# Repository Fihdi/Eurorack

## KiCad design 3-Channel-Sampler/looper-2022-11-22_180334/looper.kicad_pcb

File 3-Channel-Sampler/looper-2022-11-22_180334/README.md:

3 Channel Sampler that pairs well with the A, B and C outputs of my sequencer

This module sounds really bad because I used ISD1820 ICs for the sampling, which are low quality. I made a new Project "SimpleSampler" that uses a Daisy Seed to store and play Samples.

Known Issue: The solder points for the buttons are too close to the hole.
When the push button is stuck through the PCB and tightend with a washer, the washer will make contact with both solder points and the button is effectively always pressed.
I have put some small sheets of isolating rubber underneath the buttons to prevent this issue.

The summing amplifier should have a gain of two since the ISD1820 are running on 5V and are rather quiet compared to normal eurorack levels.

Sources and Inspiration:

https://bastl-instruments.com/support/tutorials/omsynth-project-3
https://www.youtube.com/watch?v=epjCe3o5BPA

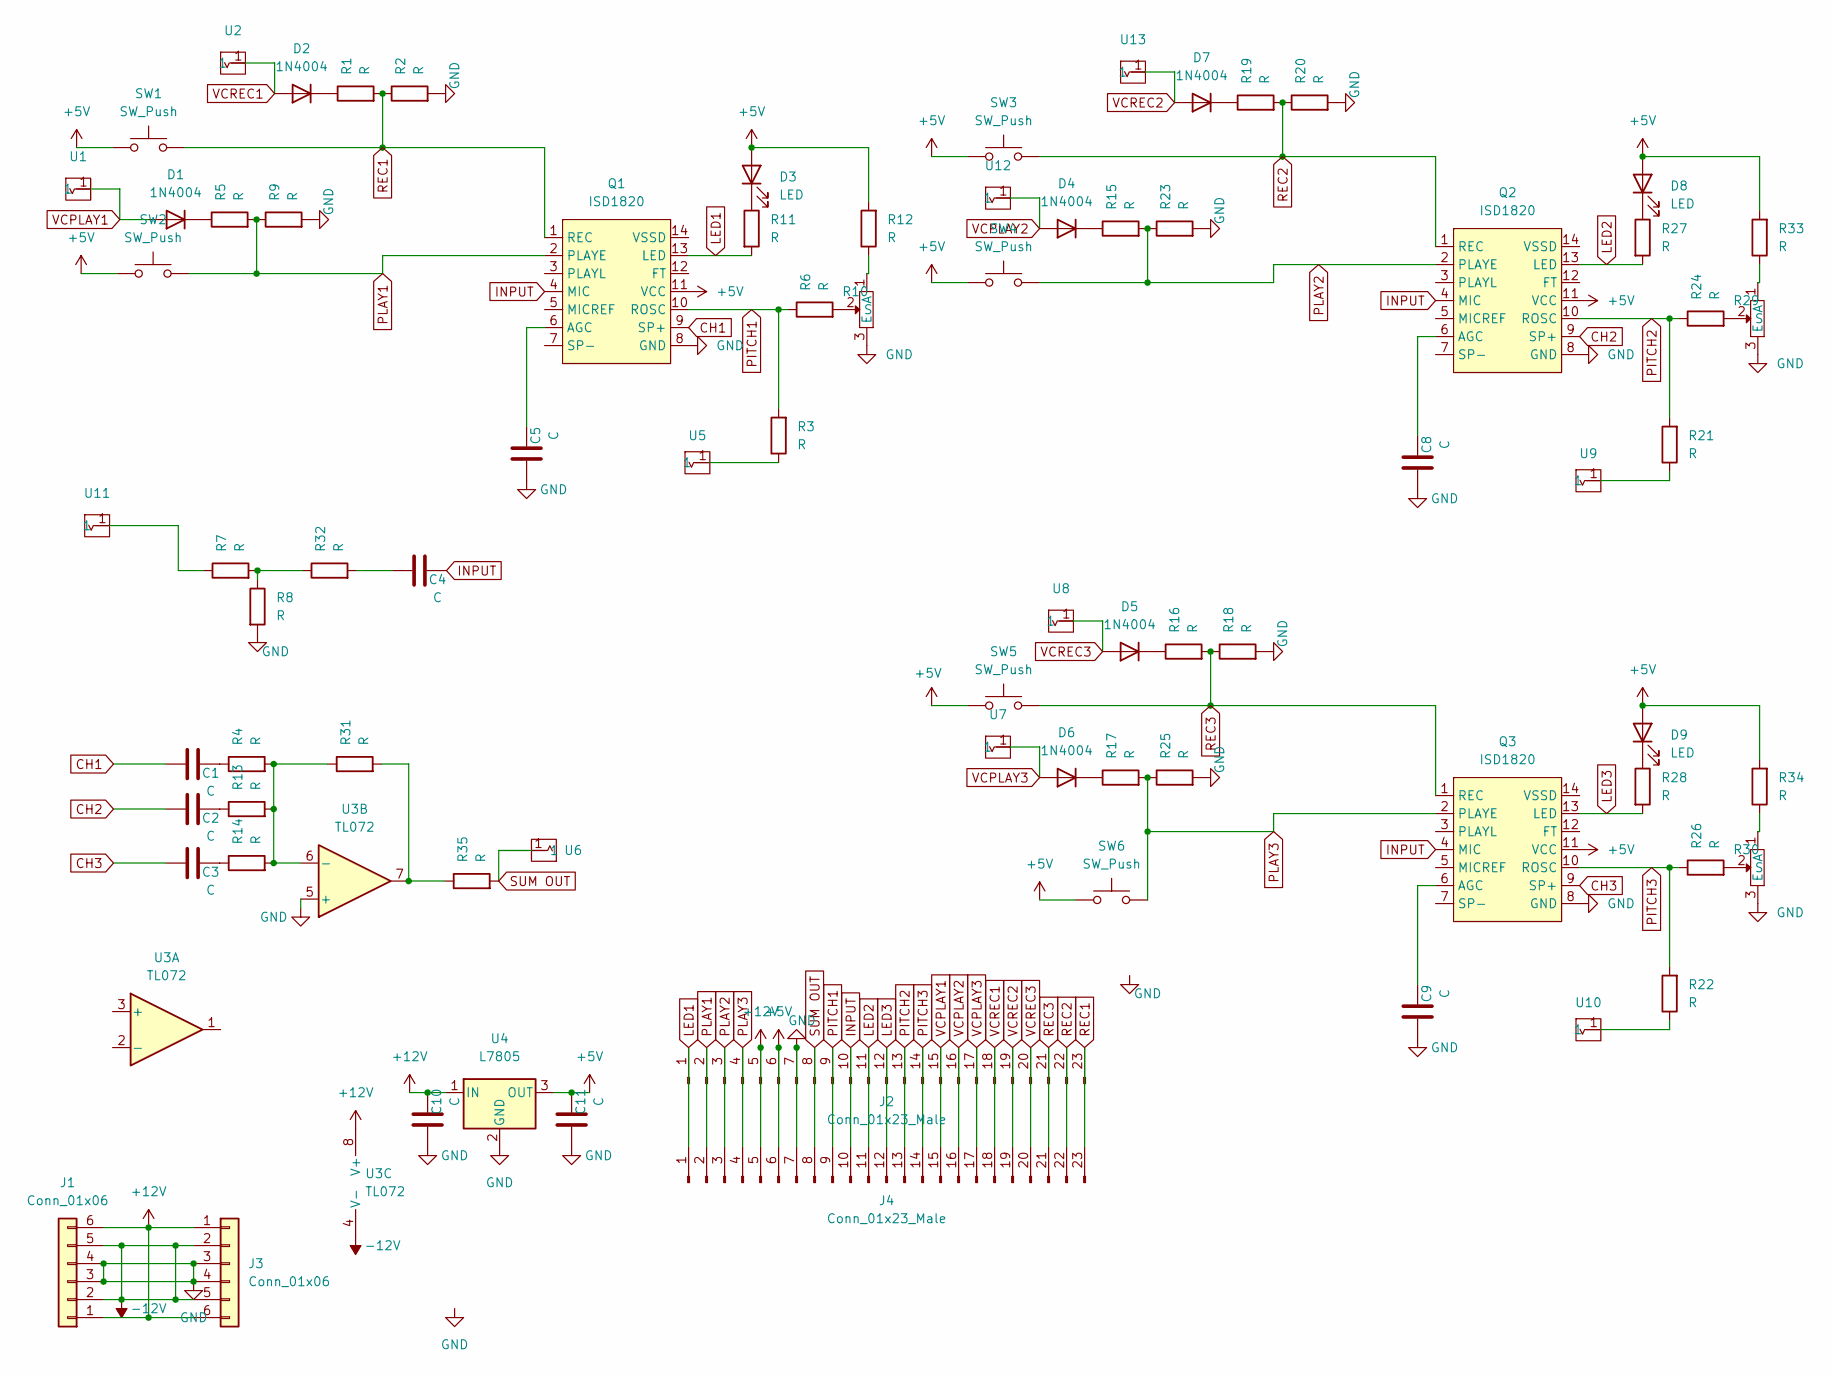
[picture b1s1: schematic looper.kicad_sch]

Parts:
C1, C2, C3: C; C_Axial_L3.8mm_D2.6mm_P7.50mm_Horizontal
C4, C5, C8, C9, C10, C11: C; C_Axial_L3.8mm_D2.6mm_P10.00mm_Horizontal
D1, D2, D4, D5, D6, D7: 1N4004; D_DO-41_SOD81_P7.62mm_Horizontal
D3, D8, D9: LED; LED_D5.0mm
J1, J3: Conn_01x06; PinHeader_1x06_P2.54mm_Vertical
J2, J4: Conn_01x23_Male; PinHeader_1x23_P2.54mm_Vertical
Q1, Q2, Q3: ISD1820; DIP-14_W7.62mm
R1, R2, R3, R4, R5, R6, R7, R8, R9, R11, R12, R13, R14, R15, R16, R17, R18, R19, R20, R21, R22, R23, R24, R25, R26, R27, R28, R31, R32, R33, R34, R35: R; R_Axial_DIN0207_L6.3mm_D2.5mm_P10.16mm_Horizontal
R10, R29, R30: AlpsPot
SW1, SW2, SW3, SW4, SW5, SW6: SW_Push; PushButton
U1, U2, U5, U6, U7, U8, U9, U10, U11, U12, U13: Aux_flush; aux_flush
U3: TL072; DIP-8_W7.62mm_Socket
U4: L7805; TO-220-3_Vertical

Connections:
+5V: C11.2, D3.2 (A), D8.2 (A), D9.2 (A), J2.6, J4.6, Q1.11 (VCC), Q2.11 (VCC), Q3.11 (VCC), R12.2, R33.2, R34.2, SW1.1, SW2.1, SW3.1, SW4.1, SW5.1, SW6.1, U4.3 (OUT)
+12V: C10.2, J1.1, J1.6, J2.5, J3.1, J3.6, J4.5, U3.8 (V+), U4.1 (IN)
-12V: J1.2, J1.5, J3.2, J3.5, U3.4 (V-)
CH1: C1.1, Q1.9 (SP+)
CH2: C2.1, Q2.9 (SP+)
CH3: C3.1, Q3.9 (SP+)
GND: C5.1, C8.1, C9.1, C10.1, C11.1, J1.3, J1.4, J2.7, J3.3, J3.4, J4.7, Q1.8 (GND), Q2.8 (GND), Q3.8 (GND), R2.2, R8.2, R9.2, R10.3 (E), R18.2, R20.2, R23.2, R25.2, R29.3 (E), R30.3 (E), U3.5 (+), U4.2 (GND)
INPUT: C4.2, J2.10, J4.10, Q1.4 (MIC), Q2.4 (MIC), Q3.4 (MIC)
LED1: J2.1, J4.1, Q1.13 (LED), R11.2
LED2: J2.11, J4.11, Q2.13 (LED), R27.2
LED3: J2.12, J4.12, Q3.13 (LED), R28.2
unnamed: C1.2, R4.1
unnamed: C2.2, R13.1
unnamed: C3.2, R14.1
unnamed: C4.1, R32.2
unnamed: C5.2, Q1.6 (AGC)
unnamed: C8.2, Q2.6 (AGC)
unnamed: C9.2, Q3.6 (AGC)
unnamed: D1.1 (K), R5.1
unnamed: D2.1 (K), R1.1
unnamed: D3.1 (K), R11.1
unnamed: D4.1 (K), R15.1
unnamed: D5.1 (K), R16.1
unnamed: D6.1 (K), R17.1
unnamed: D7.1 (K), R19.1
unnamed: D8.1 (K), R27.1
unnamed: D9.1 (K), R28.1
unnamed: R3.1, U5.1
unnamed: R7.1, U11.1
unnamed: R10.1 (A), R12.1
unnamed: R6.2, R10.2 (S)
unnamed: R4.2, R13.2, R14.2, R31.1, U3.6 (-)
unnamed: R21.1, U9.1
unnamed: R22.1, U10.1
unnamed: R24.2, R29.2 (S)
unnamed: R26.2, R30.2 (S)
unnamed: R29.1 (A), R33.1
unnamed: R30.1 (A), R34.1
unnamed: R31.2, R35.1, U3.7
unnamed: R7.2, R8.1, R32.1
PITCH1: J2.9, J4.9, Q1.10 (ROSC), R3.2, R6.1
PITCH2: J2.13, J4.13, Q2.10 (ROSC), R21.2, R24.1
PITCH3: J2.14, J4.14, Q3.10 (ROSC), R22.2, R26.1
PLAY1: J2.2, J4.2, Q1.2 (PLAYE), R5.2, R9.1, SW2.2
PLAY2: J2.3, J4.3, Q2.2 (PLAYE), R15.2, R23.1, SW4.2
PLAY3: J2.4, J4.4, Q3.2 (PLAYE), R17.2, R25.1, SW6.2
REC1: J2.23, J4.23, Q1.1 (REC), R1.2, R2.1, SW1.2
REC2: J2.22, J4.22, Q2.1 (REC), R19.2, R20.1, SW3.2
REC3: J2.21, J4.21, Q3.1 (REC), R16.2, R18.1, SW5.2
SUM OUT: J2.8, J4.8, R35.2, U6.1
VCPLAY1: D1.2 (A), J2.15, J4.15, U1.1
VCPLAY2: D4.2 (A), J2.16, J4.16, U12.1
VCPLAY3: D6.2 (A), J2.17, J4.17, U7.1
VCREC1: D2.2 (A), J2.18, J4.18, U2.1
VCREC2: D7.2 (A), J2.19, J4.19, U13.1
VCREC3: D5.2 (A), J2.20, J4.20, U8.1

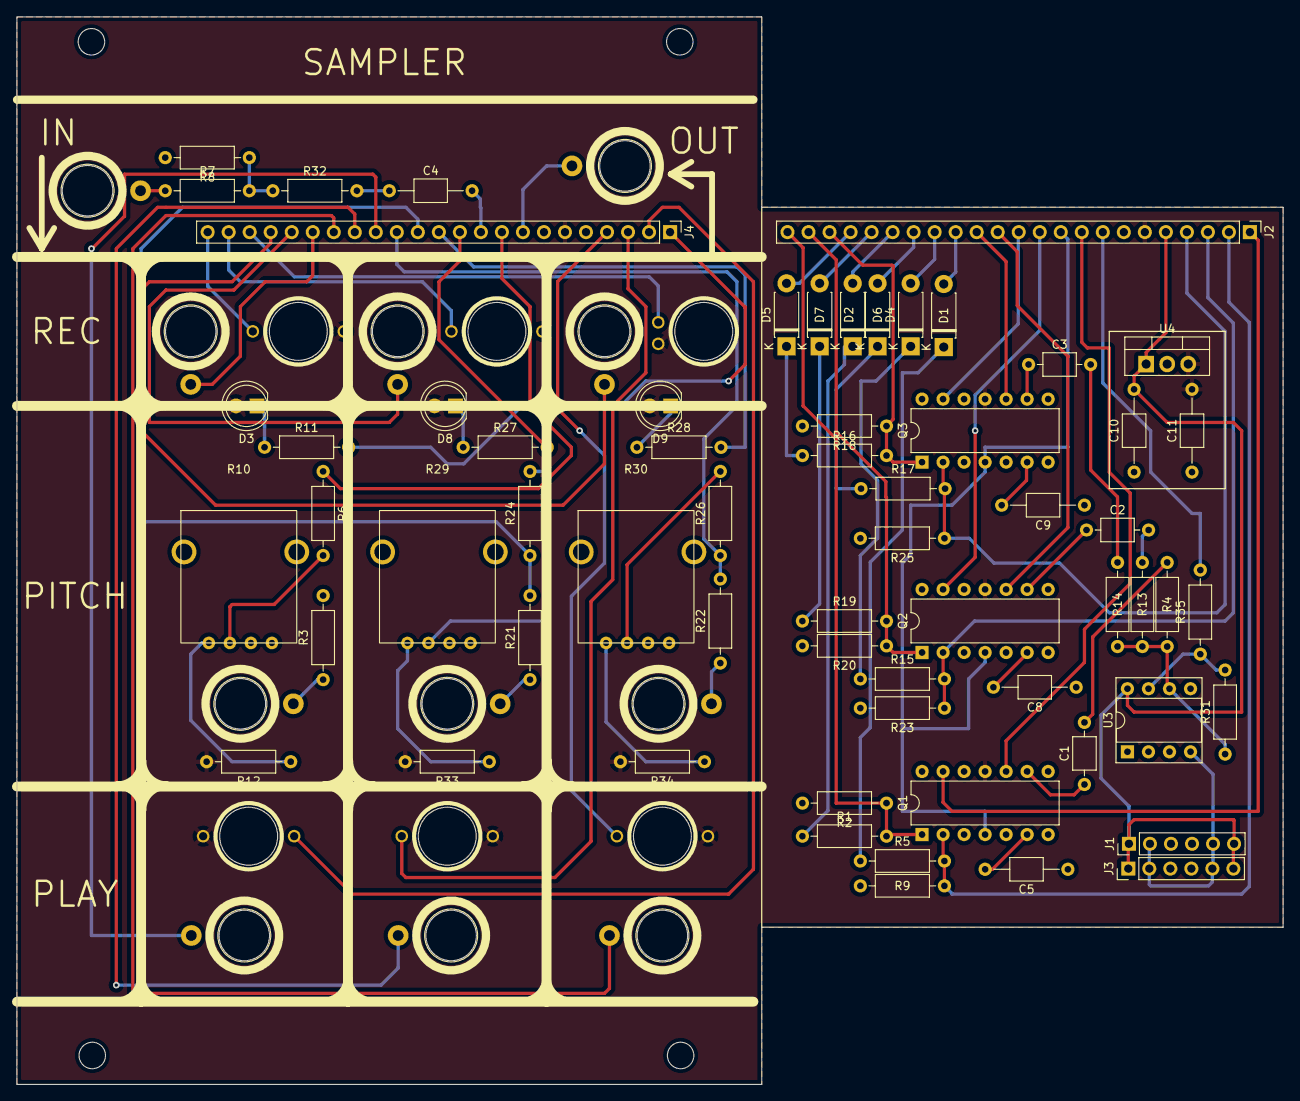
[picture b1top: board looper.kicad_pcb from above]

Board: 2 copper layers, 153.0 x 129.0 mm, 79 parts (0 on the bottom side), 56 nets.

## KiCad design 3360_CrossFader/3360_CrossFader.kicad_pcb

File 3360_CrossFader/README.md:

# 10hp Voltage Controlled Crossfader

Crossfader that can fade between two audio or CV signals. Two VCA cores that can be used together (Locked mode) or seperately (Free mode).

The "FADE" output always sums both Outputs together, regardless of the mode.

I plan on making a third board, kind of like a shield, that can be inserted into the AS3360 IC socket. This shield should replace the 3360 with an equivalent VCA circuit with regular parts like the TL074. This is because the AS3360 IC is rather scarce and expensive since it is only produced by one company, Alfa Semiconductors, Latvia.

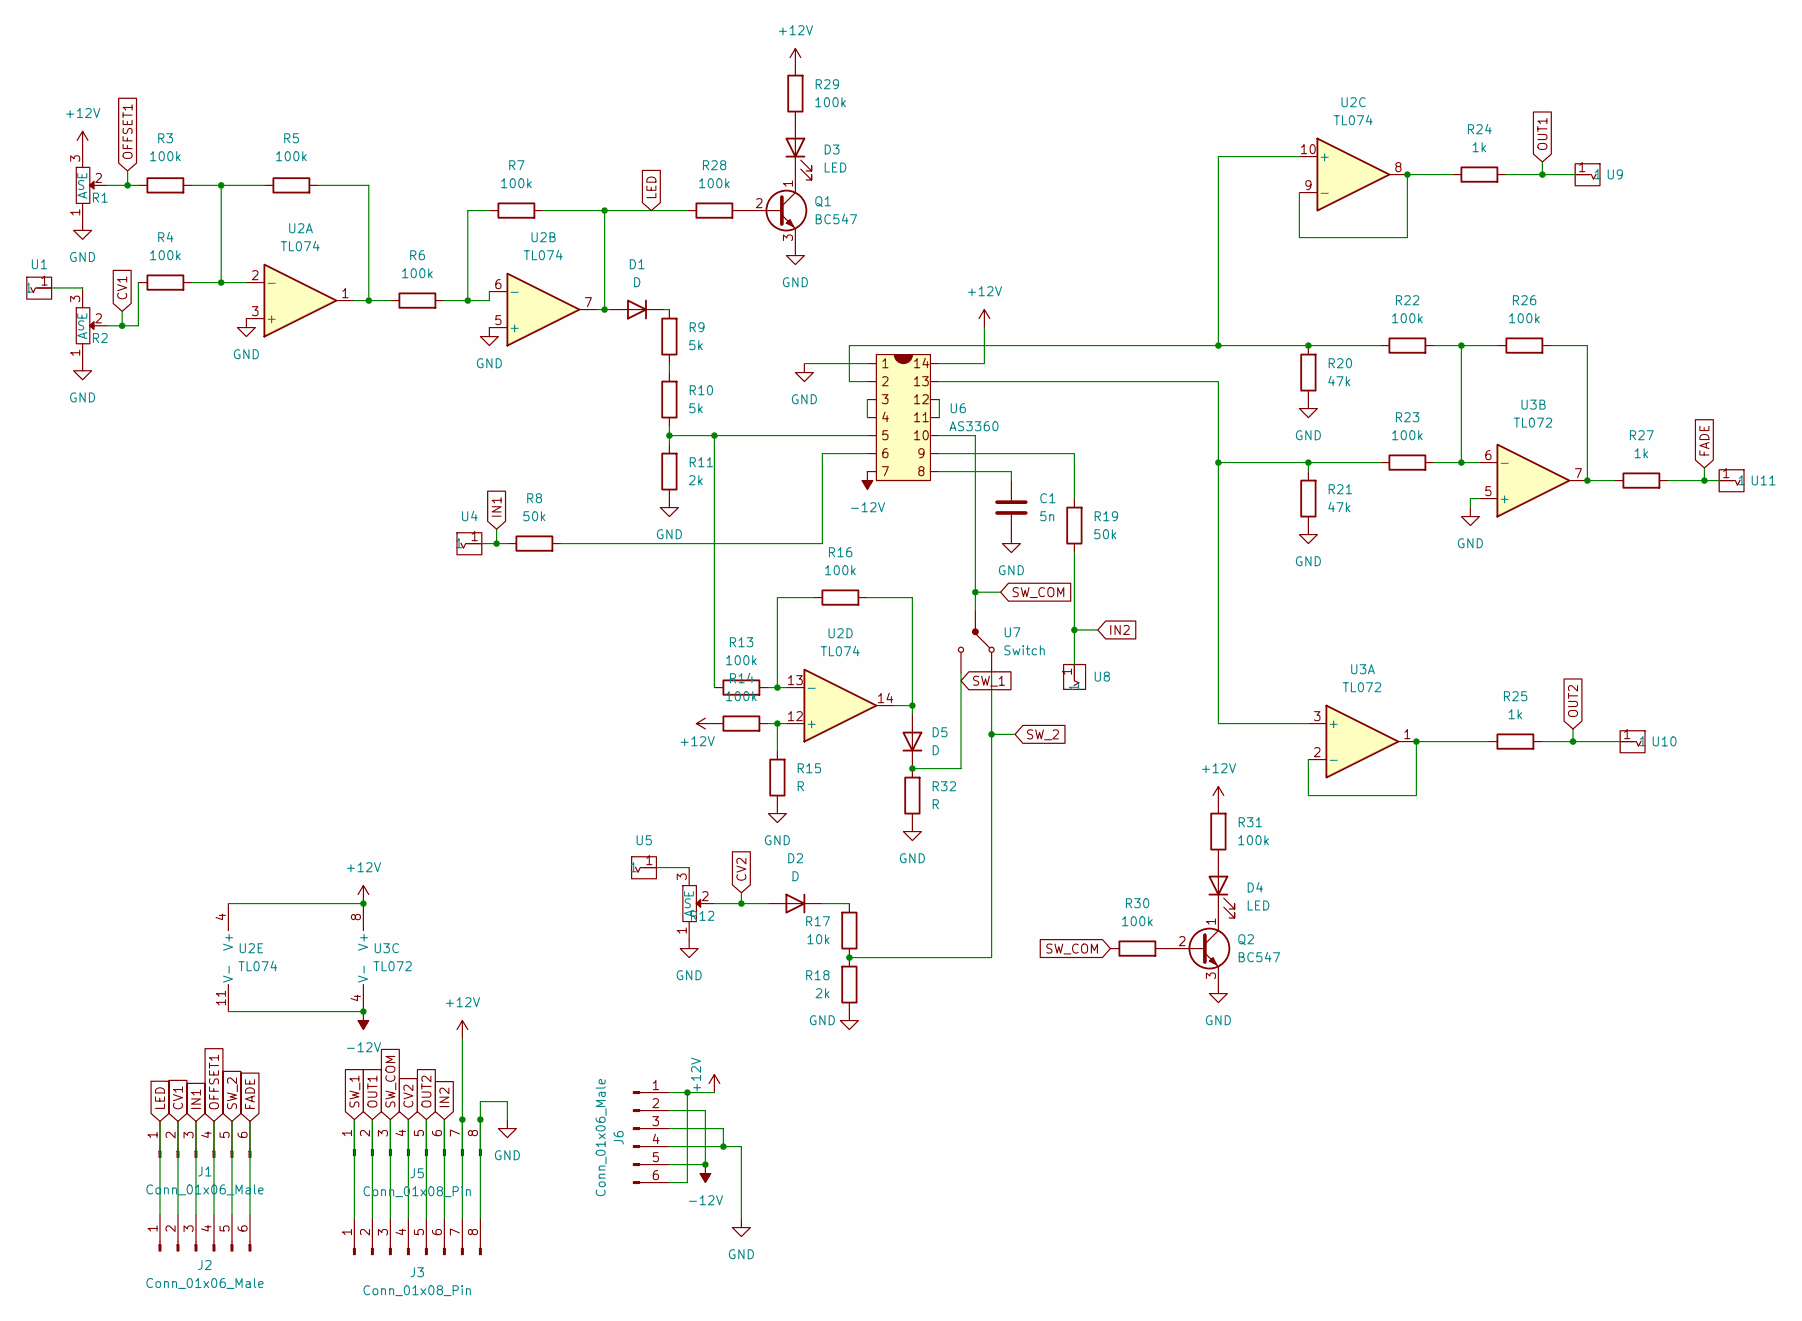
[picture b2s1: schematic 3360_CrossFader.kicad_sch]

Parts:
C1: 5n; C_Axial_L5.1mm_D3.1mm_P12.50mm_Horizontal
D1, D2: D; D_A-405_P7.62mm_Horizontal
D3, D4: LED; LED_D5.0mm
D5: D; R_Axial_DIN0207_L6.3mm_D2.5mm_P10.16mm_Horizontal
J1, J2, J6: Conn_01x06_Male; PinHeader_1x06_P2.54mm_Vertical
J3, J5: Conn_01x08_Pin; PinHeader_1x08_P2.54mm_Vertical
Q1, Q2: BC547; TO-92_Inline_Wide
R1, R2, R12: AlpsPot
R3, R4, R5, R6, R7, R13, R14, R16, R22, R23, R26, R28, R29, R30, R31: 100k; R_Axial_DIN0207_L6.3mm_D2.5mm_P10.16mm_Horizontal
R8, R19: 50k; R_Axial_DIN0207_L6.3mm_D2.5mm_P10.16mm_Horizontal
R9, R10: 5k; R_Axial_DIN0207_L6.3mm_D2.5mm_P10.16mm_Horizontal
R11, R18: 2k; R_Axial_DIN0207_L6.3mm_D2.5mm_P10.16mm_Horizontal
R15, R32: R; R_Axial_DIN0207_L6.3mm_D2.5mm_P10.16mm_Horizontal
R17: 10k; R_Axial_DIN0207_L6.3mm_D2.5mm_P10.16mm_Horizontal
R20, R21: 47k; R_Axial_DIN0207_L6.3mm_D2.5mm_P10.16mm_Horizontal
R24, R25, R27: 1k; R_Axial_DIN0207_L6.3mm_D2.5mm_P10.16mm_Horizontal
U1, U4, U5, U8, U9, U10, U11: Aux_flush; 3mm5 Mono Aux
U2: TL074; DIP-14_W7.62mm_Socket
U3: TL072; DIP-8_W7.62mm
U6: AS3360; DIP-14_W7.62mm_Socket
U7: Switch

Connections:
+12V: J3.7, J5.7, J6.1, J6.6, R1.3 (E), R14.1, R29.2, R31.2, U2.4 (V+), U3.8 (V+), U6.14
-12V: J6.2, J6.5, U2.11 (V-), U3.4 (V-), U6.7
CV1: J1.2, J2.2, R2.2 (S), R4.1
CV2: D2.2 (A), J3.4, J5.4, R12.2 (S)
FADE: J1.6, J2.6, R27.2, U11.1
GND: C1.2, J3.8, J5.8, J6.3, J6.4, Q1.3 (E), Q2.3 (E), R1.1 (A), R2.1 (A), R11.1, R12.1 (A), R15.1, R18.1, R20.1, R21.1, R32.1, U2.3 (+), U2.5 (+), U3.5 (+), U6.1
IN1: J1.3, J2.3, R8.1, U4.1
IN2: J3.6, J5.6, R19.1, U8.1
LED: D1.2 (A), J1.1, J2.1, R7.2, R28.1, U2.7
unnamed: C1.1, U6.8
unnamed: D1.1 (K), R9.2
unnamed: D2.1 (K), R17.2
unnamed: D3.2 (A), R29.1
unnamed: D3.1 (K), Q1.1 (C)
unnamed: D4.2 (A), R31.1
unnamed: D4.1 (K), Q2.1 (C)
unnamed: D5.2 (A), R16.2, U2.14
unnamed: Q1.2 (B), R28.2
unnamed: Q2.2 (B), R30.2
unnamed: R2.3 (E), U1.1
unnamed: R5.2, R6.1, U2.1
unnamed: R8.2, U6.6
unnamed: R10.1, R11.2, R13.1, U6.5
unnamed: R9.1, R10.2
unnamed: R12.3 (E), U5.1
unnamed: R19.2, U6.9
unnamed: R26.2, R27.1, U3.7
unnamed: R3.2, R4.2, R5.1, U2.2 (-)
unnamed: R6.2, R7.1, U2.6 (-)
unnamed: R20.2, R22.1, U2.10 (+), U6.2
unnamed: R24.1, U2.8, U2.9 (-)
unnamed: R14.2, R15.2, U2.12 (+)
unnamed: R13.2, R16.1, U2.13 (-)
unnamed: R21.2, R23.1, U3.3 (+), U6.13
unnamed: R25.1, U3.1, U3.2 (-)
unnamed: R22.2, R23.2, R26.1, U3.6 (-)
unnamed: U6.3, U6.4
unnamed: U6.11, U6.12
OFFSET1: J1.4, J2.4, R1.2 (S), R3.1
OUT1: J3.2, J5.2, R24.2, U9.1
OUT2: J3.5, J5.5, R25.2, U10.1
SW_1: D5.1 (K), J3.1, J5.1, R32.2, U7.3
SW_2: J1.5, J2.5, R17.1, R18.2, U7.1
SW_COM: J3.3, J5.3, R30.1, U6.10, U7.2

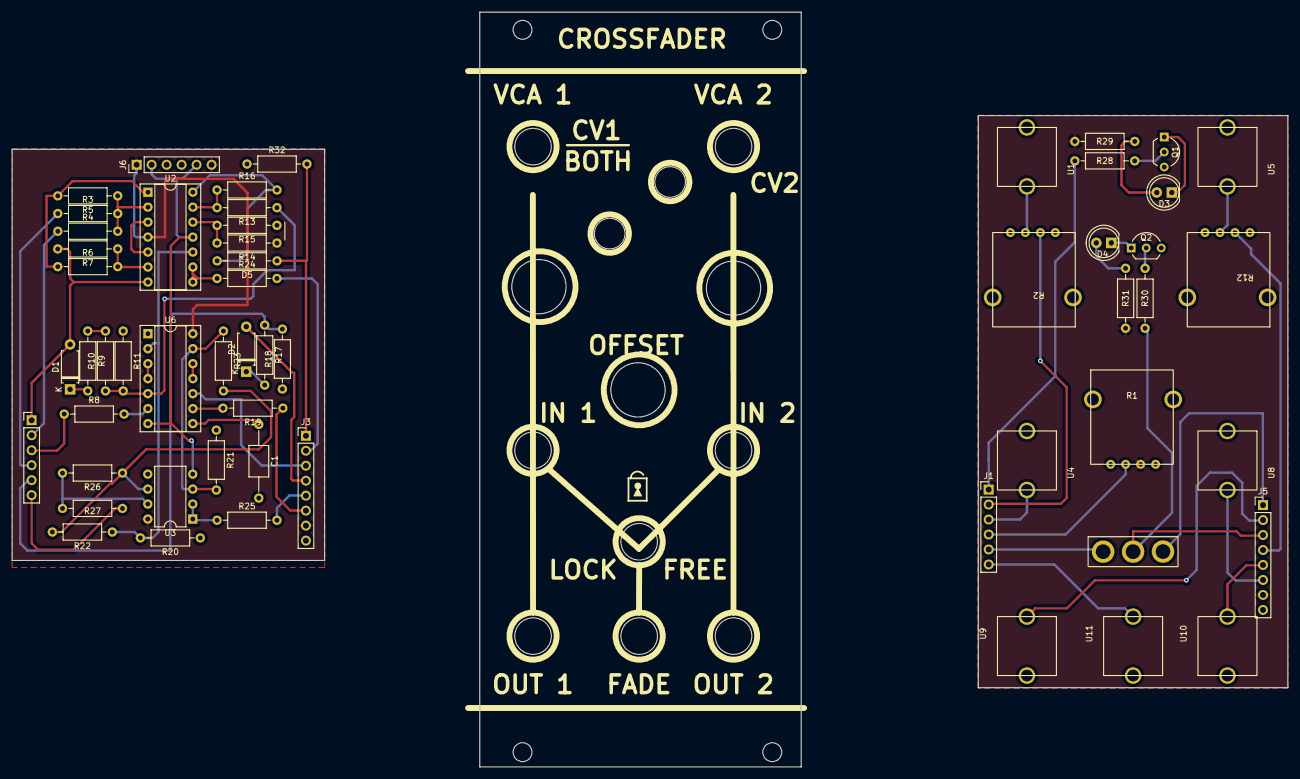
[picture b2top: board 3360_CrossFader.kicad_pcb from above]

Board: 2 copper layers, 216.3 x 128.0 mm, 56 parts (0 on the bottom side), 44 nets.

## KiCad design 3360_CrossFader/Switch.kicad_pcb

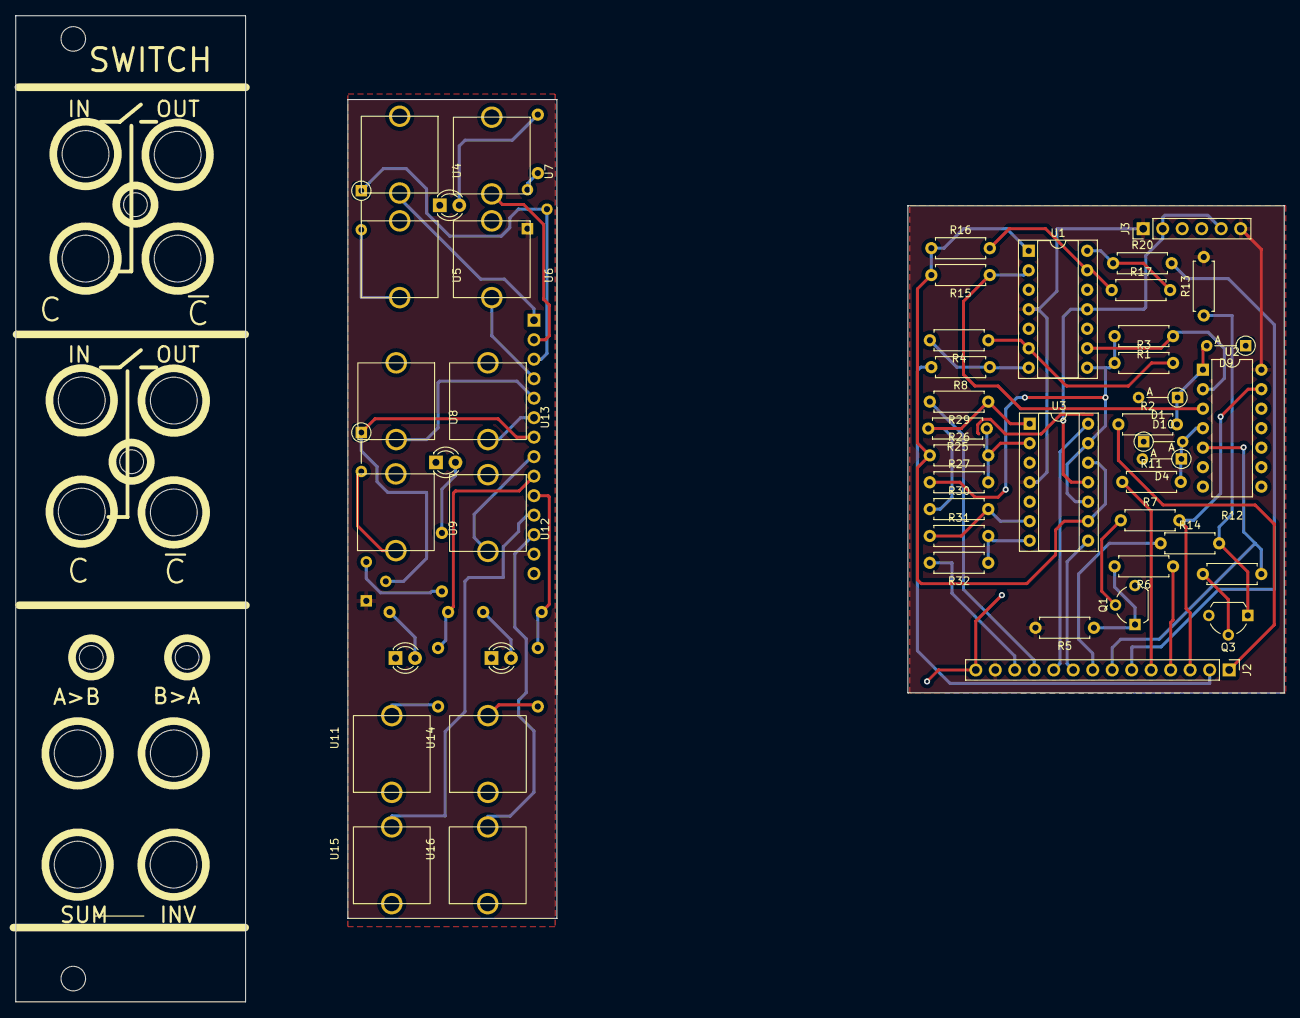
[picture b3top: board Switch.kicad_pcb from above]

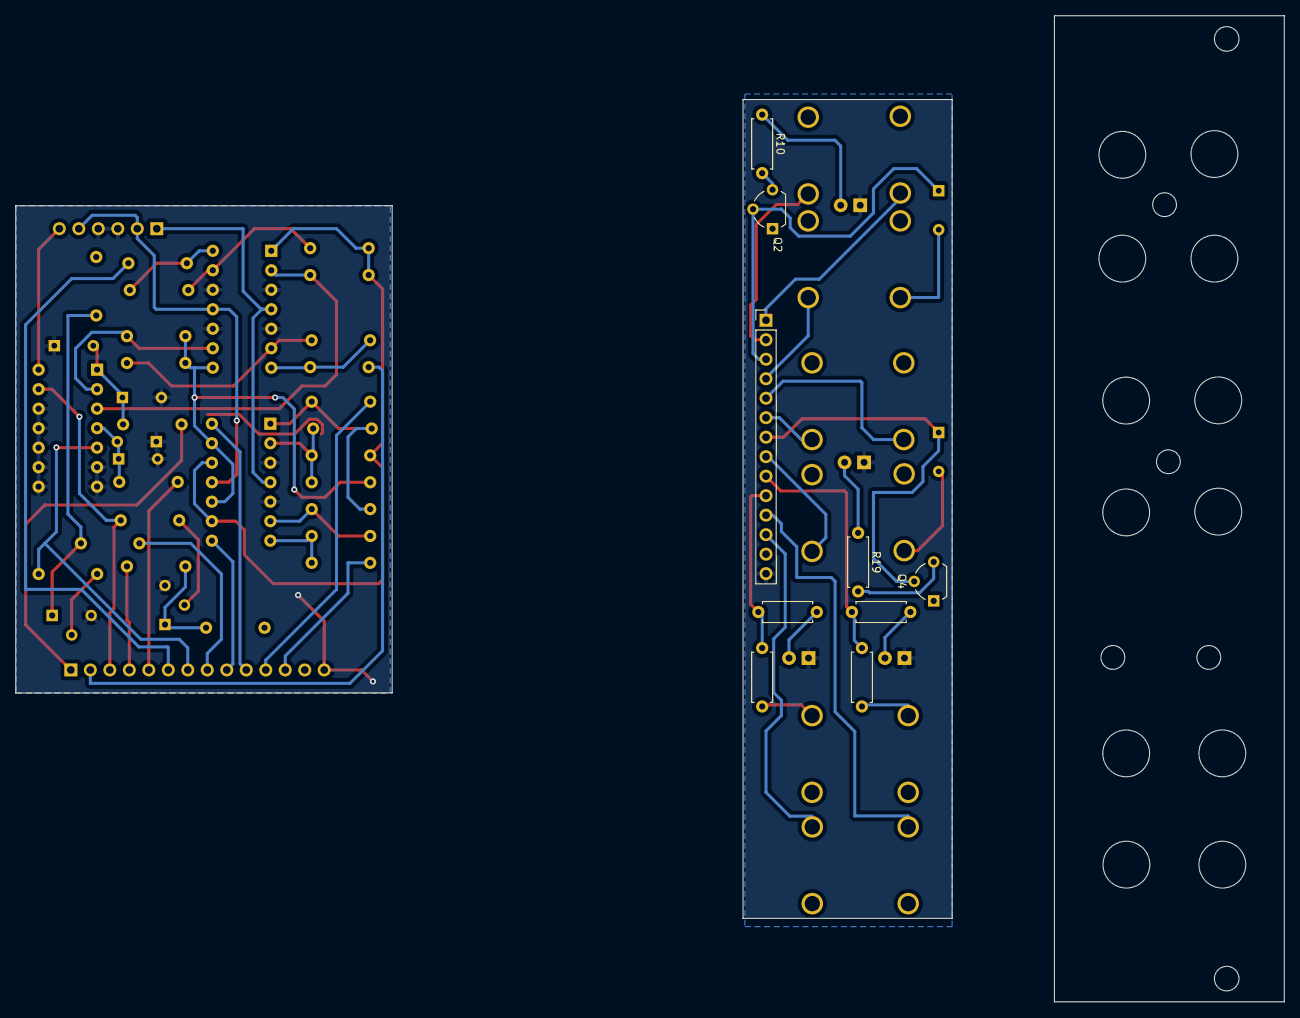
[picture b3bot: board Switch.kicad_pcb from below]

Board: 2 copper layers, 165.3 x 128.5 mm, 61 parts (9 on the bottom side), 43 nets.

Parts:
D1, D2, D4, D5, D9, D10: D; D_DO-34_SOD68_P5.08mm_Vertical_AnodeUp
D3, D6, D7, D8: LED; LED_D3.0mm
J1, J2: Conn_01x14_Pin; PinHeader_1x14_P2.54mm_Vertical
J3: Conn_01x06_Pin; PinHeader_1x06_P2.54mm_Vertical
Q1, Q2, Q3, Q4: BC547; TO-92L_Wide
R1, R2, R3, R4, R5, R6, R7, R8, R9, R10, R11, R12, R13, R14, R15, R16, R17, R18, R19, R20, R21, R22, R25, R26, R27, R29, R30, R31, R32: R; R_Axial_DIN0207_L6.3mm_D2.5mm_P7.62mm_Horizontal
U1, U3: TL074; DIP-14_W7.62mm_Socket
U2: CD4066BE; DIP-14_W7.62mm
U4, U5, U6, U7, U8, U9, U11, U12, U13, U14, U15, U16: Aux_flush; 3mm5 Mono Aux

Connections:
+12V: J1.13, J2.13, J3.1, J3.6, Q2.1 (C), Q4.1 (C), R5.2, R13.2, U1.4 (V+), U2.14 (V_{DD}), U3.4 (V+)
-12V: J3.2, J3.5, U1.11 (V-), U3.11 (V-)
AB: J1.9, J2.9, R9.2, R18.1, U3.8
BA: J1.10, J2.10, R21.2, R22.1, U3.14
C1: D2.1 (K), J1.3, J2.3, Q2.2 (B), R7.2, U2.13
C2: D5.1 (K), J1.7, J2.7, Q4.2 (B), R12.2, U2.5
GND: D1.2 (A), D3.1 (K), D4.2 (A), D6.1 (K), D7.1 (K), D8.1 (K), D9.1 (K), D10.1 (K), J1.14, J2.14, J3.3, J3.4, Q1.3 (E), Q3.3 (E), U1.3 (+), U1.5 (+), U1.10 (+), U1.12 (+), U2.6, U2.7 (V_{SS}), U2.8, U2.9, U2.10, U2.11, U2.12, U3.3 (+), U3.5 (+)
IN1: J1.1, J2.1, R2.1, U4.1
IN2: J1.5, J2.5, R11.1, U8.1
INV1: J1.4, J2.4, R6.1, U6.1
INV2: J1.8, J2.8, R14.1, U12.1
unnamed: D1.1 (K), D9.2 (A), R2.2, U2.1
unnamed: D2.2 (A), U5.1
unnamed: D3.2 (A), R10.1
unnamed: D5.2 (A), U9.1
unnamed: D6.2 (A), R19.1
unnamed: D7.2 (A), R9.1
unnamed: D8.2 (A), R21.1
unnamed: D4.1 (K), D10.2 (A), R11.2, U2.4
unnamed: Q1.2 (B), R7.1
unnamed: Q1.1 (C), R5.1, R6.2
unnamed: Q2.3 (E), R10.2
unnamed: Q3.2 (B), R12.1
unnamed: Q3.1 (C), R13.1, R14.2
unnamed: Q4.3 (E), R19.2
unnamed: R4.2, R8.1, U1.7
unnamed: R17.2, R20.1, U1.14
unnamed: R18.2, U11.1
unnamed: R22.2, U14.1
unnamed: R25.2, R29.1, R30.1, U3.1
unnamed: R31.2, R32.1, U3.7
unnamed: R15.1, U1.2 (-), U2.3
unnamed: R3.2, R4.1, U1.6 (-)
unnamed: R1.1, U1.9 (-), U2.2
unnamed: R16.2, R17.1, U1.13 (-)
unnamed: R25.1, R26.2, R27.2, U3.2 (-)
unnamed: R30.2, R31.1, U3.6 (-)
OUT1: J1.2, J2.2, R8.2, U7.1
OUT2: J1.6, J2.6, R20.2, U13.1
S1: R1.2, R3.1, R27.1, U1.8, U3.10 (+), U3.13 (-)
S2: R15.2, R16.1, R26.1, U1.1, U3.9 (-), U3.12 (+)
SUM: J1.11, J2.11, R29.2, U15.1
SUM_INV: J1.12, J2.12, R32.2, U16.1

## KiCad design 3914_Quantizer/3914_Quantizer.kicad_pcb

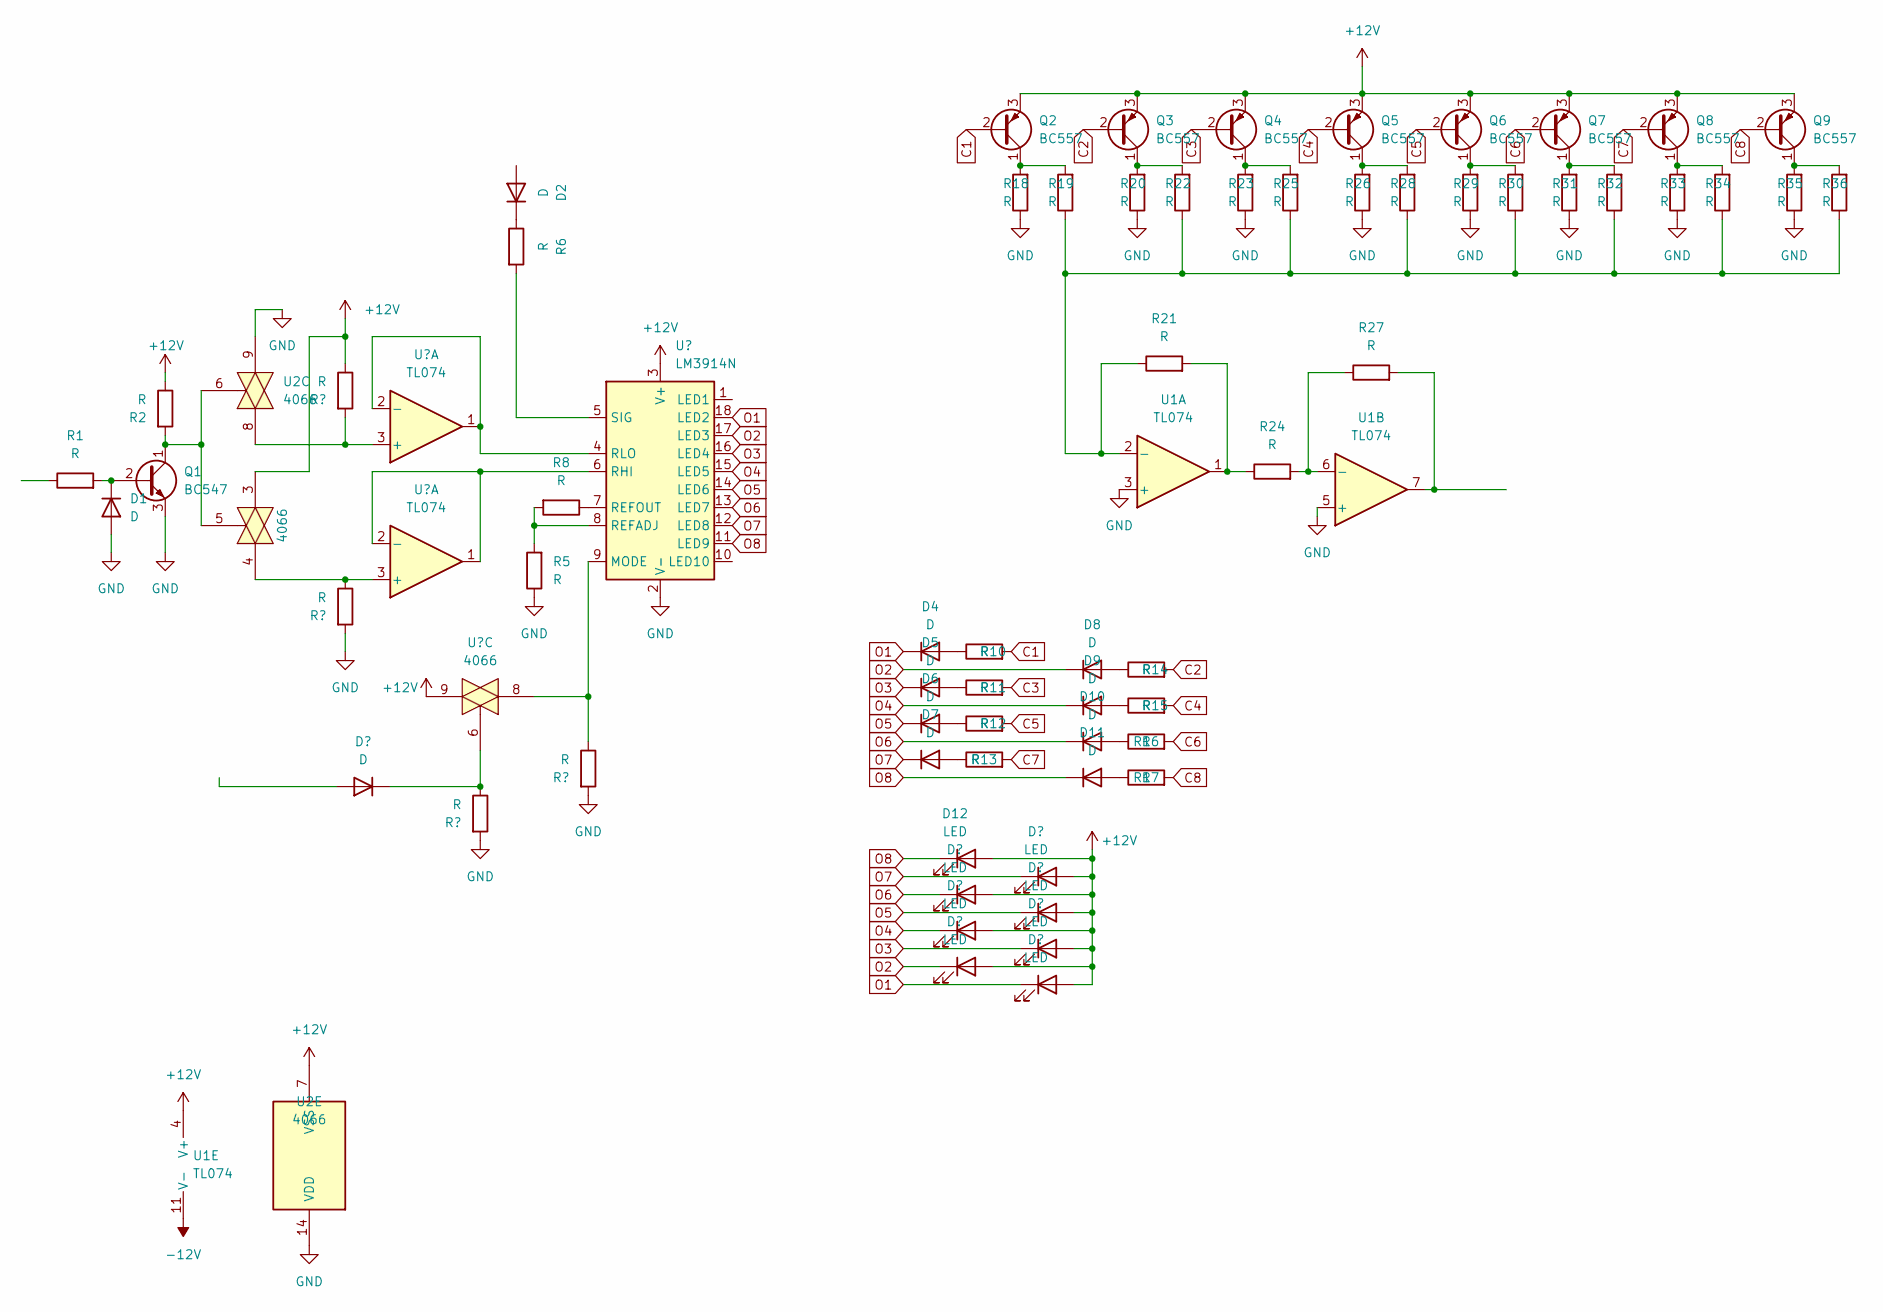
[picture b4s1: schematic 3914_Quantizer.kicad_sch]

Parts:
D1, D2, D4, D5, D6, D7, D8, D9, D10, D11: D; D_A-405_P10.16mm_Horizontal
D12: LED; LED_D5.0mm
Q1: BC547; TO-92_Inline
Q2, Q3, Q4, Q5, Q6, Q7, Q8, Q9: BC557; TO-92_Inline
R1, R2, R5, R6, R8, R10, R11, R12, R13, R14, R15, R16, R17, R18, R19, R20, R21, R22, R23, R24, R25, R26, R27, R28, R29, R30, R31, R32, R33, R34, R35, R36: R; R_Axial_DIN0207_L6.3mm_D2.5mm_P10.16mm_Horizontal
U1: TL074; DIP-14_W7.62mm
U2: 4066; DIP-14_W7.62mm_Socket

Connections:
+12V: Q2.3 (E), Q3.3 (E), Q4.3 (E), Q5.3 (E), Q6.3 (E), Q7.3 (E), Q8.3 (E), Q9.3 (E), R2.1, U2.2, U2.9; also elsewhere on the board
C1: Q2.2 (B), R10.2
C2: Q3.2 (B), R14.2
C3: Q4.2 (B), R11.2
C4: Q5.2 (B), R15.2
C5: Q6.2 (B), R12.2
C6: Q7.2 (B), R16.2
C7: Q8.2 (B), R13.2
C8: Q9.2 (B), R17.2
GND: D1.2 (A), Q1.3 (E), R5.1, R18.1, R20.1, R23.1, R26.1, R29.1, R31.1, R33.1, R35.1, U1.3 (+), U1.5 (+), U2.3; also elsewhere on the board
unnamed 10: D4.1 (K); also elsewhere on the board
unnamed: D4.2 (A), R10.1
unnamed: Q1.1 (C), R2.2, U2.5, U2.6
unnamed: D1.1 (K), Q1.2 (B), R1.2
unnamed: Q2.1 (C), R18.2, R19.2
unnamed: Q3.1 (C), R20.2, R22.2
unnamed: Q4.1 (C), R23.2, R25.2
unnamed: Q5.1 (C), R26.2, R28.2
unnamed: Q6.1 (C), R29.2, R30.2
unnamed: Q7.1 (C), R31.2, R32.2
unnamed: Q8.1 (C), R33.2, R34.2
unnamed: Q9.1 (C), R35.2, R36.2
unnamed 22: U2.4; also elsewhere on the board
unnamed 23: U2.8; also elsewhere on the board
unnamed 24: R5.2, R8.2; also elsewhere on the board
unnamed: D2.1 (K), R6.1
unnamed 26: R6.2; also elsewhere on the board
unnamed 27: U2.13; also elsewhere on the board
unnamed 28: R8.1; also elsewhere on the board
unnamed 29: U2.1; also elsewhere on the board
unnamed: D5.2 (A), R11.1
unnamed: D6.2 (A), R12.1
unnamed: D7.2 (A), R13.1
unnamed: D8.2 (A), R14.1
unnamed: D9.2 (A), R15.1
unnamed: D10.2 (A), R16.1
unnamed: D11.2 (A), R17.1
unnamed: R19.1, R21.1, R22.1, R25.1, R28.1, R30.1, R32.1, R34.1, R36.1, U1.2 (-)
unnamed: R21.2, R24.1, U1.1
unnamed: R24.2, R27.1, U1.6 (-)
unnamed: R27.2, U1.7
unnamed 41: D11.1 (K), D12.1 (K); also elsewhere on the board
unnamed 42: D7.1 (K); also elsewhere on the board
unnamed 43: D10.1 (K); also elsewhere on the board
unnamed 44: D6.1 (K); also elsewhere on the board
unnamed 45: D9.1 (K); also elsewhere on the board
unnamed 46: D5.1 (K); also elsewhere on the board
unnamed 47: D8.1 (K); also elsewhere on the board

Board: 2 copper layers, 60 parts (0 on the bottom side), 48 nets, no tracks yet.

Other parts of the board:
D3: D; D_A-405_P10.16mm_Horizontal
R3, R4, R7, R9: R; R_Axial_DIN0207_L6.3mm_D2.5mm_P10.16mm_Horizontal
U3: LM3914N; DIP-18_W7.62mm

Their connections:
+12V: R3.1, U3.3 (V+); also elsewhere on the board
GND: R4.1, R7.1, R9.1, U3.2 (V-); also elsewhere on the board
unnamed 10: U3.1 (LED1); also elsewhere on the board
unnamed 22: R3.2, U3.4 (RLO); also elsewhere on the board
unnamed 23: R4.2, U3.6 (RHI); also elsewhere on the board
unnamed 24: U3.8 (REFADJ); also elsewhere on the board
unnamed 26: U3.5 (SIG); also elsewhere on the board
unnamed 27: D3.1 (K), R7.2; also elsewhere on the board
unnamed 28: U3.7 (REFOUT); also elsewhere on the board
unnamed 29: R9.2, U3.9 (MODE); also elsewhere on the board
unnamed 41: U3.12 (LED8); also elsewhere on the board
unnamed 42: U3.13 (LED7); also elsewhere on the board
unnamed 43: U3.14 (LED6); also elsewhere on the board
unnamed 44: U3.15 (LED5); also elsewhere on the board
unnamed 45: U3.16 (LED4); also elsewhere on the board
unnamed 46: U3.17 (LED3); also elsewhere on the board
unnamed 47: U3.18 (LED2); also elsewhere on the board
